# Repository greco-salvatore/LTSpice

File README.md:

## Elettronica industriale

piccolo approfondimento sugli oscillatori, in particolare il 555

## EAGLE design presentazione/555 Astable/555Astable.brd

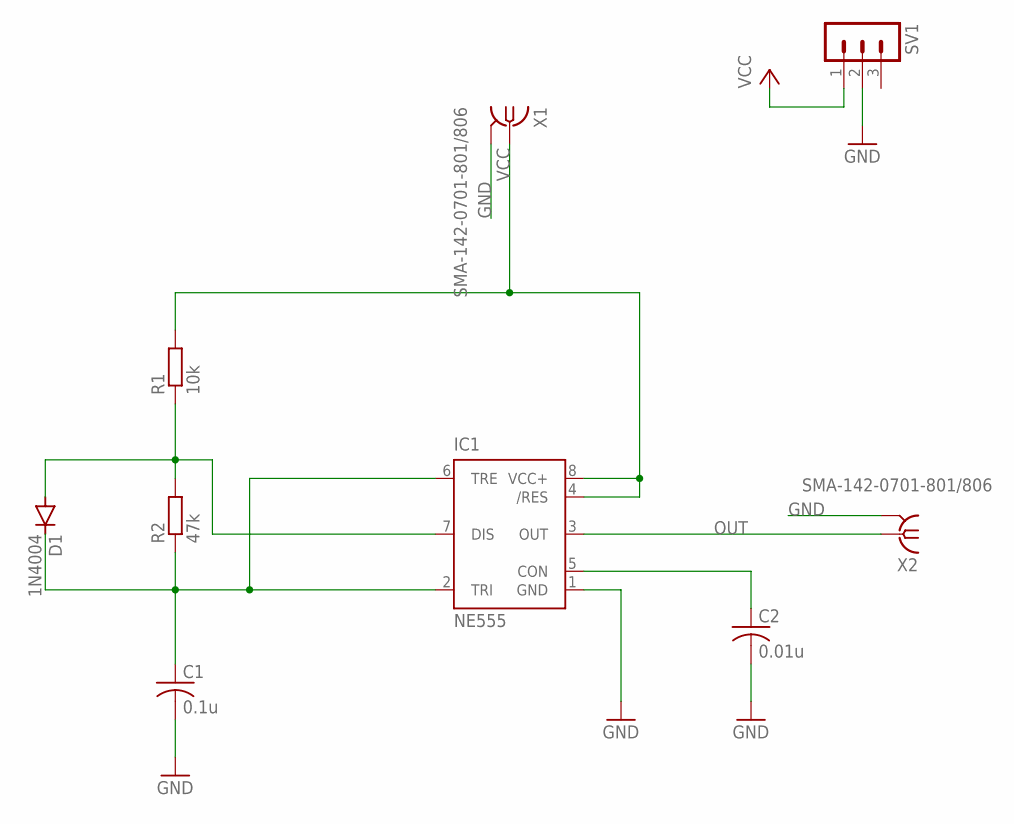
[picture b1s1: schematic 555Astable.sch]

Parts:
C1: 0.1u; C0504
C2: 0.01u; C0504
D1: 1N4004; DO41-10
IC1: NE555; DIL-08
R1: 10k; R0805
R2: 47k; R0805
SV1: MA03-1
X1, X2: SMA-142-0701-801/806; J502-ND-142-0701-801/806

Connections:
GND: C1.2, C2.2, IC1.1 (GND), SV1.2, X1.G@1 (2), X1.G@2 (2), X1.G@3 (2), X1.G@4 (2), X2.G@1 (2), X2.G@2 (2), X2.G@3 (2), X2.G@4 (2)
unnamed: C2.1, IC1.5 (CON)
unnamed: C1.1, D1.C, IC1.2 (TRI), IC1.6 (TRE), R2.1
unnamed: D1.A, IC1.7 (DIS), R1.1, R2.2
OUT: IC1.3 (OUT), X2.1
VCC: IC1.4 (/RES), IC1.8 (VCC+), R1.2, SV1.1, X1.1

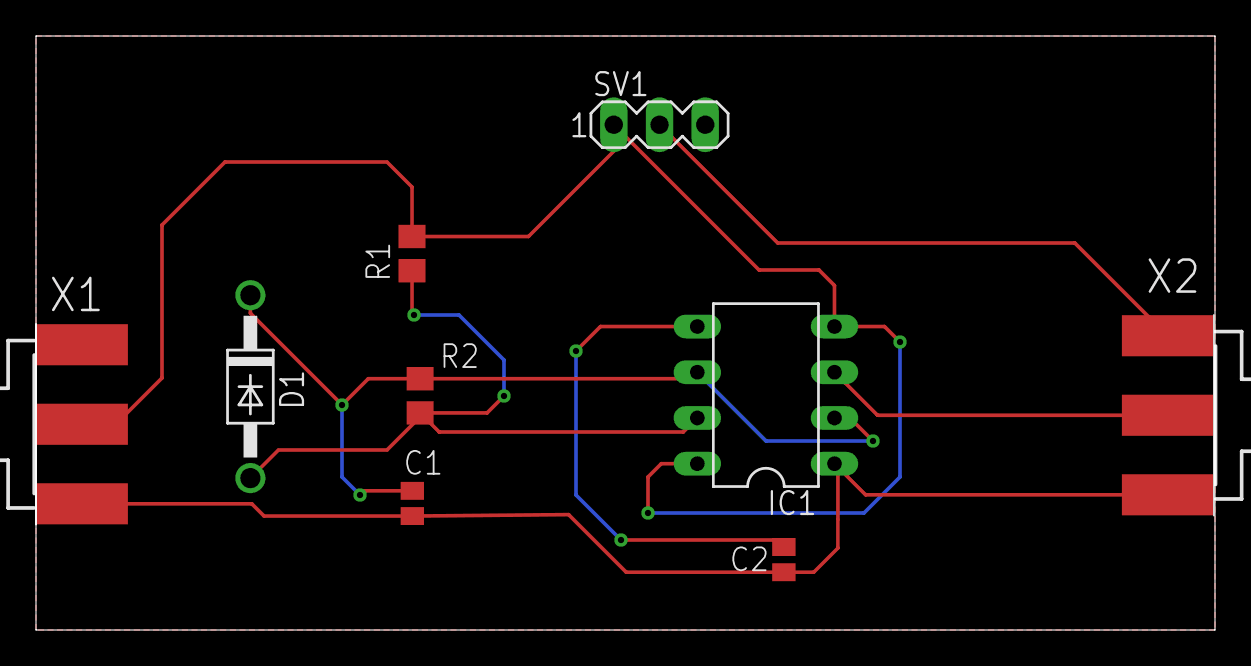
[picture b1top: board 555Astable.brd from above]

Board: 2 copper layers, 65.5 x 33.0 mm, 9 parts (0 on the bottom side), 6 nets.

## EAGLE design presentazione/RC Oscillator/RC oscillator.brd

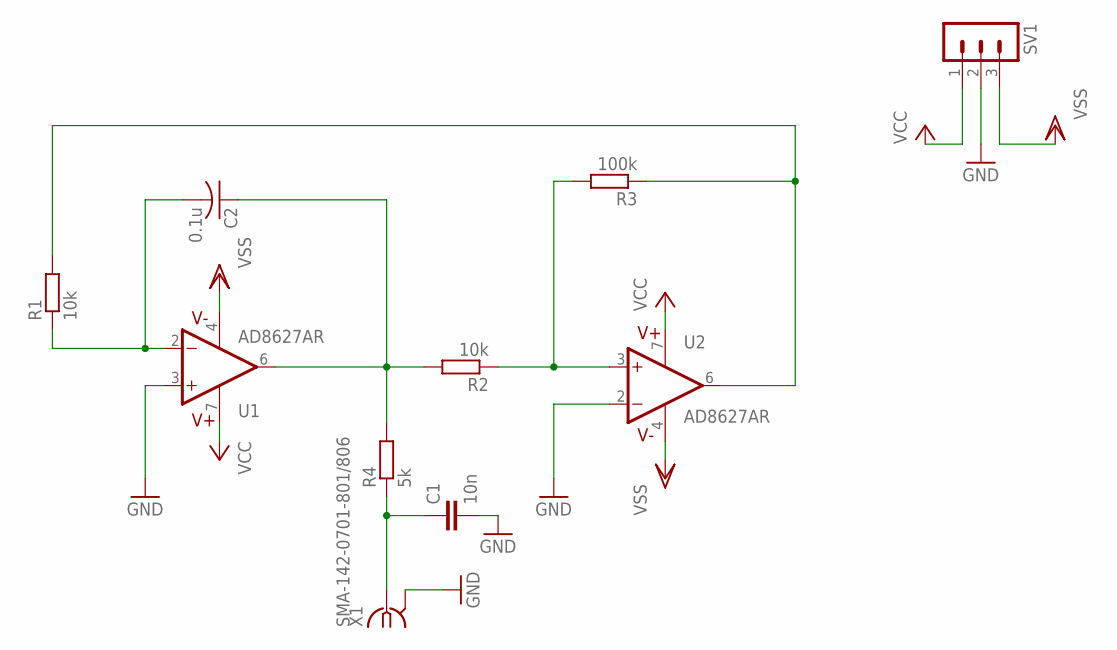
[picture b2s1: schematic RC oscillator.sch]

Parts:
C1: 10n; C025-030X050
C2: 0.1u; C0504
R1, R2: 10k; R0805
R3: 100k; R0805
R4: 5k; R0805
SV1: MA03-1
U1, U2: AD8627AR; SOIC8
X1: SMA-142-0701-801/806; J502-ND-142-0701-801/806

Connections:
GND: C1.2, SV1.2, U1.3 (+IN), U2.2 (-IN), X1.G@1 (2), X1.G@2 (2), X1.G@3 (2), X1.G@4 (2)
unnamed: C2.2, R1.1, U1.2 (-IN)
unnamed: R1.2, R3.1, U2.6 (OUT)
unnamed: C2.1, R2.2, R4.2, U1.6 (OUT)
unnamed: R2.1, R3.2, U2.3 (+IN)
unnamed: C1.1, R4.1, X1.1
VCC: SV1.1, U1.7 (V+), U2.7 (V+)
VSS: SV1.3, U1.4 (V-), U2.4 (V-)

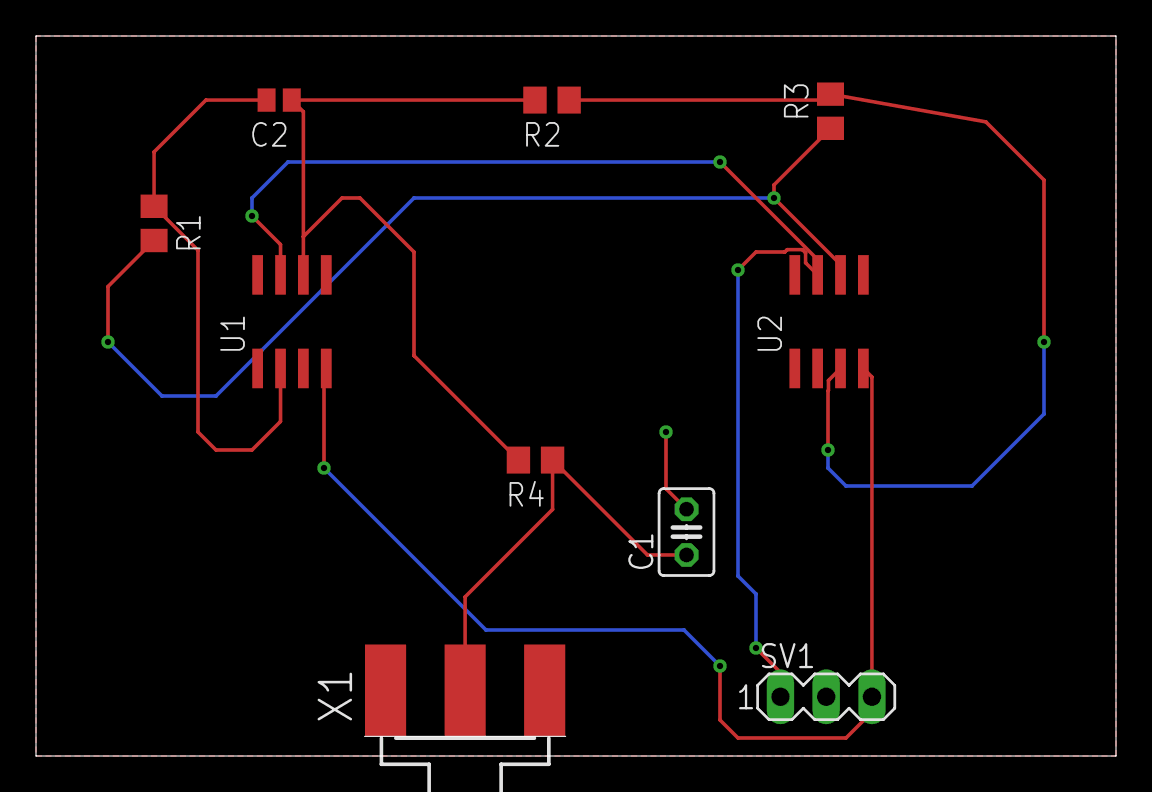
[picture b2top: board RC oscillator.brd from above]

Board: 2 copper layers, 60.0 x 40.0 mm, 10 parts (0 on the bottom side), 8 nets.

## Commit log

2022-05-24 init repo
2022-05-31 update2
2022-06-27 presentazione + RCoscillator
2022-07-04 presentazione
2022-07-04 presentazione pdf
